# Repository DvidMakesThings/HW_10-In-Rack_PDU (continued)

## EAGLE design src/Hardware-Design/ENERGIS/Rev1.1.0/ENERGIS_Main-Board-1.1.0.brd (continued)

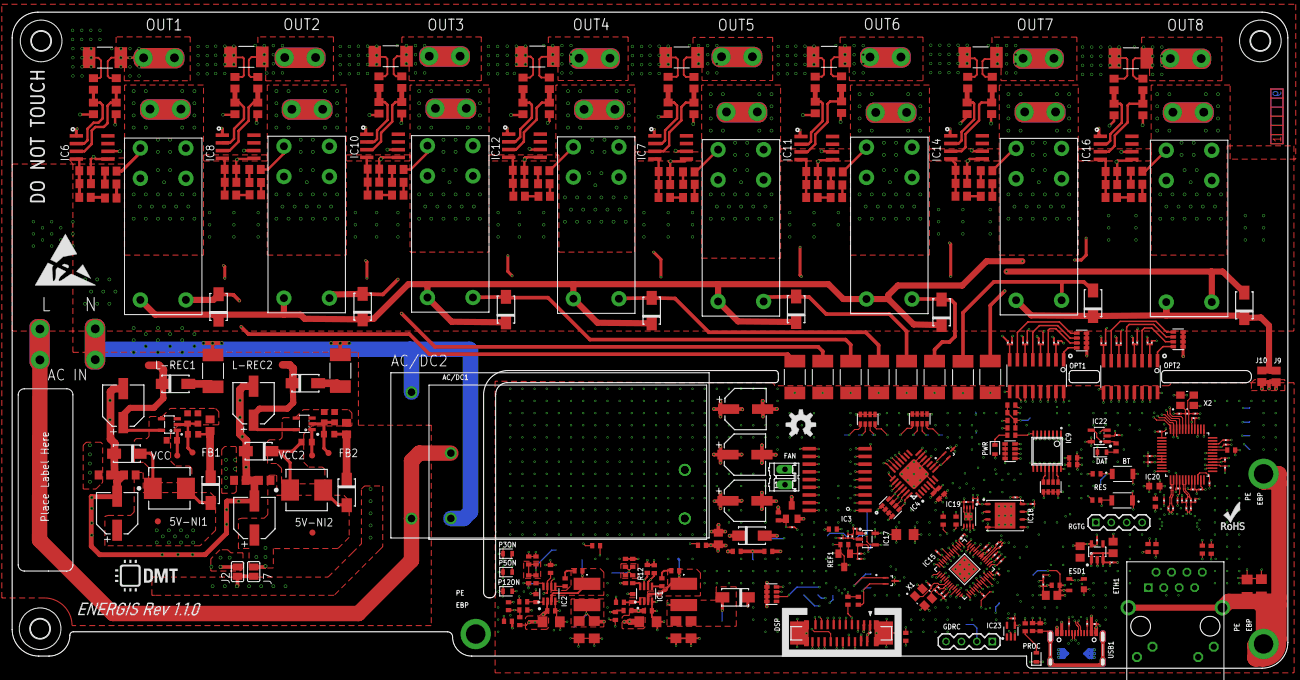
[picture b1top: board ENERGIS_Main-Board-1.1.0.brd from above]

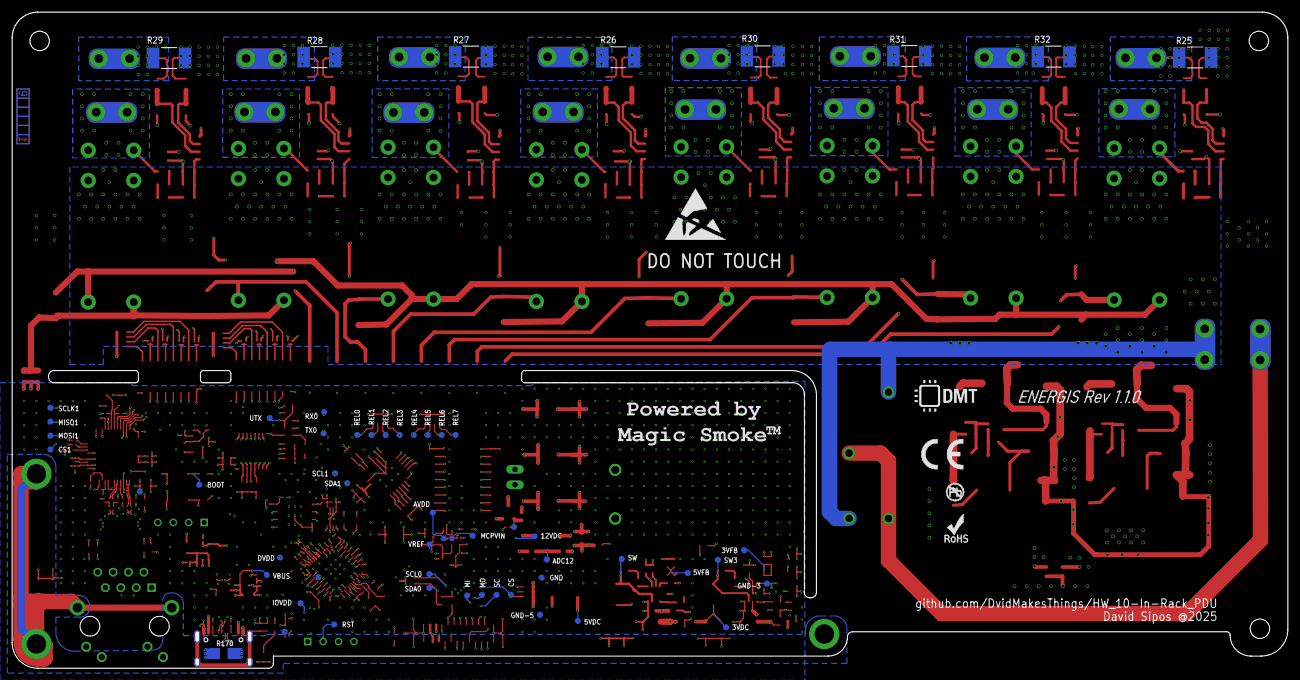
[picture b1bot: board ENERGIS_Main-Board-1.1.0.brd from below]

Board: 6 copper layers, 210.0 x 108.0 mm, 455 parts (62 on the bottom side), 254 nets.

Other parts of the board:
U$1, U$2: DNI; ESD_10.00
U$3, U$4, U$6: DNI; 3,2
U$5, U$7: DNI; DMT
U$10: DNI; OSHW-LOGO-M
U$11, U$14: DNI; ROHS_LOGO_0.18_IN
U$12: DNI; CE_5MM
U$13: DNI; NO_PB_LOGO_0.120
U$15: DNI; SMOKE

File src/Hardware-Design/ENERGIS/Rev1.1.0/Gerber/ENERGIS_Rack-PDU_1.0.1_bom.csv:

Comment,Designator,Footprint,LCSC Part #
0.002R 1%,R25 R26 R27 R28 R29 R30 R31 R32 R35 R43 R51 R67 R75 R83 R99 R115,2512,C728320
0R 1%,J8 J9 J10,0805,C17477
0R 1%,R17 R18 R19 R20 R21 R22 R23 R24,2512,C25469
0R 1%,R57 R91,0402,C17168
1K 1%,R16,0201,C270365
1K 1%,R33 R34 R40 R41 R42 R48 R49 R50 R56,0805,C17513
1K 1%,R59,0201,C270365
1K 1%,R63 R64,_0603X4-1206,C110021
1K 1%,R65 R66 R72 R73 R74 R80 R81 R82 R88 R97 R98 R104,0805,C17513
1K 1%,R112,0402,C11702
1K 1%,R113 R114 R120,0805,C17513
1K 1%,R122 R123 R151,0402,C11702
1K 1%,R153 R154 R155 R156 R157 R158 R159,0201,C270365
1K 1%,R163,0402,C11702
1M 1%,R110,1206,C17927
1M 1%,R131,0402,C26083
1M 1%,R144,0201,C295786
1N4007,D9 D10 D12 D13,SMA/DO-214AC,C727081
1mH,L3 L5,L-6.6X6.6,C168049
1nF 25V,C106 C107 C108 C109 C110 C111 C112 C113,0201,C7694325V
1nF 50V,C5 C51,0603,C1588
1uF 16V,C102,0201,C307385
1uF 25V,C60 C104,0402,C52923
1uF 50V,C45 C57,0805,C28323
2.2K 1%,R121,0201,C473508
2.2uF 50V,C21 C46,0603,C913904
2.2uF 400V,C35 C47,6.3X7.7(DXL),C3345109
2.4K 1%,R148,0402,C25882
3.3K 1%,R130 R149,_0603X4-1206,C1734380
3.3R 1%,R133 R134 R135 R136,0201,C158547
4.2uH,L2,SRR5228A,
4.7K 1%,R109 R129 R145,0201,C270346
4.7nF 50V,C78,0402,C1538
4.7uF 25V,C85,0402,C22367824
4.9uH,L1,SRR5228A,
4.99K 1%,R60 R61 R105 R107,0603,C23046
5.1K 1%,R124 R125,0201,C274341
6.8nF 50V,C81 C82,0201,C285015
7.5K 1%,R6 R12,0402,C25918
8.2K 1%,R150,0402,C25924
9.09K 1%,R4,0402,C11549
10K 1%,R2,0402,C25744
10K 1%,R89 R90 R93,_0603X4-1206,C110924
10K 1%,R95,0402,C25744
10K 1%,R96 R108,0805,C17414
10K 1%,R126 R127,0201,C473048
10K 1%,R132 R147 R162 R164,0402,C25744
10R 1%,R7 R9,0402,C25077
10R 1%,R152,0201,C270817
10uF 50V,C65 C97 C99,0805,C440198
12.4K 1%,R143,R0201,
12.7K 1%,R14,0402,C25853
15pF 50V,C58 C59,0201,C22374851
18pF 50V,C86 C87,0201,C62164
20K 1%,R8,0402,C25765
22nF 50V,C80,0402,C1532
22uF 25V,C1 C2 C14 C15 C17 C18,1206,C12891
25MHz,X2,WE-XTAL_CFPX-180,C9006
27R 1%,R15 R160,0201,C473051
33K,R10,0402,
33nF 50V,C24 C25 C26 C27 C28 C29 C30 C31 C32 C36 C37 C38 C39 C40 C41 C42 C43 C44 C48 C49 C50 C54 C55 C56,0805,C107150
33pF 50V,C11 C12,0402,C107005
39R 1% 2W,R62 R106,2512,C175263
40.2K 1%,R11 R13,0402,C25893
49.9R 1%,R137 R138 R139 R140,0201,C155744
100K 1%,R3 R5 R94,0402,C25741
100K 1%,RN1 RN2,_0603X4-1206,C110374
100nF 25V,C3 C4 C6 C7 C8 C9 C19 C20 C33 C34,0402,C56392
100nF 25V,C61 C62 C63 C64,0201,C76939
100nF 25V,C66,0402,C56392
100nF 25V,C67 C68 C69 C70 C71 C72 C73 C74 C75 C76 C77,0201,C76939
100nF 25V,C79,0402,C56392
100nF 25V,C84 C88 C89 C90 C91 C92 C93 C94 C95 C96 C98 C100 C101 C103,0201,C76939
100uF 25V,C10 C13 C16,6.3X7.7(DXL),C267469
100uF 50V,C23 C53,6.3X7.7(DXL),C3151829
220nF 50V,C22 C52,0805,C5378
470K 1%,R36 R37 R38 R39 R44 R45 R46 R47 R52 R53 R54 R55 R68 R69 R70 R71 R76 R77 R78 R79 R84 R85 R86 R87 R100 R101 R102 R103 R116 R117 R118 R119,0805,C17709
470R 1%,R141 R142 R146,0402,C25117
ABM8-272-T3 12MHz,X1,WE-XTAL_CFPX-180,C20625731
ACPL-247-500E ,OPT1 OPT2,SO16,C188681
AFC11-S20ICC-00 ,DSP,FPC20,C11073
B3U-1000P ,BOOT RESET,B3U-1000P,C231329
BLM18EG221TN1D,L4,0603,C113025
Blue,DAT,LED-0603,C965807
C1206C102KGRACTM,C83,C1206,
CAT24C256HU4IGT3,IC19,SON50P300X200X50-9T130X140N,C233771
DNI,R1 R58 R92,0402,
DNI,R111,R0201,
DNI,R161,0402,
G2RL-1A-E DC12 ,K1 K2 K3 K4 K5 K6 K7 K8,RELAY_G2RL-1A-E_DC5_OMR,C1564126
Green,P3ON P5ON P12ON PROC PWR,LED-0603,C965804
HLW8032,IC6 IC7 IC8 IC10 IC11 IC12 IC14 IC16,SO8,C128023
IRM-10-15 ,AC/DC2,IRM_15_12,C5439799
IRM_10_12,AC/DC1,IRM_10_12,C20618065
J1B1211CCD,ETH1,J1B1211CCD,C910371
JP,J2 J7,SJ,
LM4040B30FTA,REF1,SOT23,C460604
MBRA340T3G,D1 D2 D3 D4 D5 D6 D7 D8,SMA/DO-214AC,C26178
MCP6001RT-I/OT,IC17 IC22,SOT23-5,C154973
MCP23017T-E/ML ,IC4,QFN28[6X6]ML,C629439
MIC5504-3.3YM5 ,IC21,SOT23-5,C41348078
MOUNT-PAD-ROUND2.8,L_OUT1,2 8-PAD,
MOUNT-PAD-ROUND2.8,L_OUT2,2 8-PAD,
MOUNT-PAD-ROUND2.8,L_OUT3,2 8-PAD,
MOUNT-PAD-ROUND2.8,L_OUT4,2 8-PAD,
MOUNT-PAD-ROUND2.8,L_OUT5,2 8-PAD,
MOUNT-PAD-ROUND2.8,L_OUT6,2 8-PAD,
MOUNT-PAD-ROUND2.8,L_OUT7,2 8-PAD,
MOUNT-PAD-ROUND2.8,L_OUT8,2 8-PAD,
MOUNT-PAD-ROUND2.8,N_OUT1,2 8-PAD,
MOUNT-PAD-ROUND2.8,N_OUT2,2 8-PAD,
MOUNT-PAD-ROUND2.8,N_OUT3,2 8-PAD,
MOUNT-PAD-ROUND2.8,N_OUT4,2 8-PAD,
MOUNT-PAD-ROUND2.8,N_OUT5,2 8-PAD,
MOUNT-PAD-ROUND2.8,N_OUT6,2 8-PAD,
MOUNT-PAD-ROUND2.8,N_OUT7,2 8-PAD,
MOUNT-PAD-ROUND2.8,N_OUT8,2 8-PAD,
MOUNT-PAD-ROUND3.0,AC_L,3 0-PAD,
MOUNT-PAD-ROUND3.0,AC_N,3 0-PAD,
MP150GJ,IC5 IC13,SOT23-5,
MP2315GJ-Z ,IC1 IC2,SOT65P280X110-8N,C45889
NC,R128 R165,R0201,
RCLAMP0582BQTCT,D17 D18,SOT-523,C841193
RP2040,IC15,QFN56,C2040
SMAJ15A,D16,SMA/DO-214AC,C23424
SN74HC151PWR,IC9,TSSOP16,C2653837
SP0503BAHTG,ESD1,SOT143,C3040626
SS12,D15,SMA/DO-214AC,C727049
TP,3VDC 3VFB 5V-NI1 5V-NI2 5VDC 5VFB 12VDC AVDD CS0 CS1 DVDD FB-NI1 FB-NI2 GND GND-3 GND-5 IOVDD L-REC1 L-REC2 MISO0 MISO1 MOSI0 MOSI1 REL0 REL1 REL2 REL3 REL4 REL5 REL6 REL7 RX0 RX1 SCL0 SCL1 SCLK0 SCLK1 SDA0 SDA1 SW SW3 VBUS VNI1 VNI2 VREF,TP,
ULN2803AFWG,IC3,SO18,C845537
US1J-E3/61T ,D11 D14,SMA/DO-214AC,C44763
USB-TYPE-C-018 ,USB1,USB-C,C2927038
W25Q128JVPIQ,IC18,SON127P600X500X75-8N,C190862
W5500,IC20,LQFP48,C32843

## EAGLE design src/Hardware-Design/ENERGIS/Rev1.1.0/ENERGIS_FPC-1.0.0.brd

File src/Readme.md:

# ENERGIS - The Managed PDU Project for 10-Inch Rack - Design files

This repository contains source files for software and hardware designs related to the 10-Inch_Rack-PDU project.

## Contents

- **Software**: Source code for the software components.
- **Hardware**: Design files for the hardware components.

## Usage

1. Clone the repository.
2. Navigate to the `src` directory.
3. Follow the instructions in the respective subdirectories for software and hardware.

## License
This project is licensed under the GPL-3.0 License. See the [LICENSE](LICENSE) file for details.

## Contact
For questions or feedback:
- Email: [s.dvid@hotmail.com](mailto:s.dvid@hotmail.com)
- GitHub: [DvidMakesThings](https://github.com/DvidMakesThings)

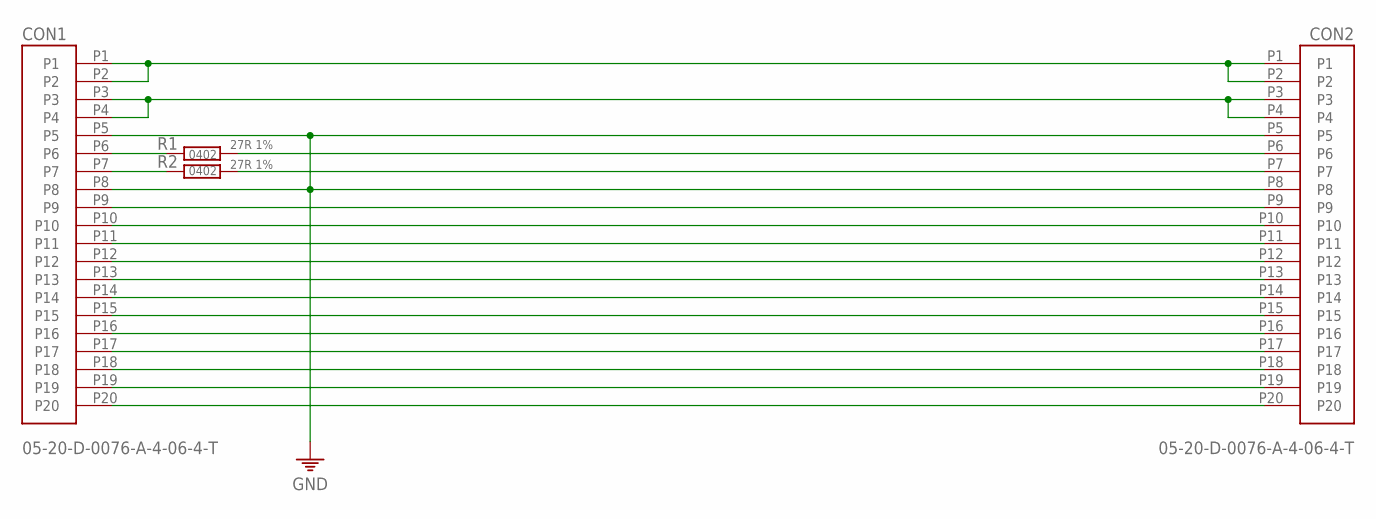
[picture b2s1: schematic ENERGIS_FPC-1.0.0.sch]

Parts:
CON1, CON2: 05-20-D-0076-A-4-06-4-T
R1, R2: 27R 1%; 0402

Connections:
GND: CON1.P5, CON1.P8, CON2.P5, CON2.P8
unnamed: CON1.P1, CON1.P2, CON2.P1, CON2.P2
unnamed: CON1.P3, CON1.P4, CON2.P3, CON2.P4
unnamed: CON1.P6, R1.1
unnamed: CON1.P7, R2.1
unnamed: CON1.P9, CON2.P9
unnamed: CON1.P10, CON2.P10
unnamed: CON1.P11, CON2.P11
unnamed: CON1.P12, CON2.P12
unnamed: CON1.P13, CON2.P13
unnamed: CON1.P14, CON2.P14
unnamed: CON1.P15, CON2.P15
unnamed: CON1.P16, CON2.P16
unnamed: CON1.P17, CON2.P17
unnamed: CON1.P18, CON2.P18
unnamed: CON1.P19, CON2.P19
unnamed: CON1.P20, CON2.P20
unnamed: CON2.P6, R1.2
unnamed: CON2.P7, R2.2

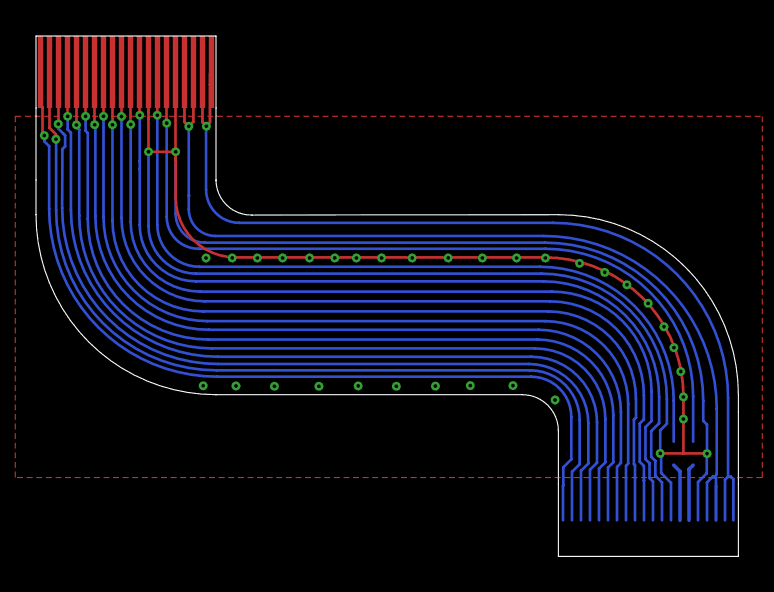
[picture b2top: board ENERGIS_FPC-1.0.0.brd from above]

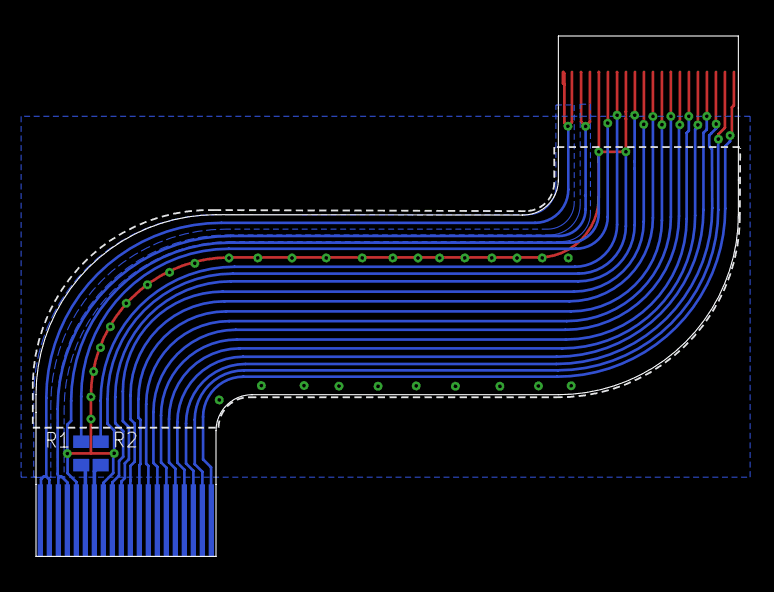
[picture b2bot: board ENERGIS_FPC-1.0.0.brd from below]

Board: 2 copper layers, 39.0 x 28.9 mm, 4 parts (3 on the bottom side), 19 nets.

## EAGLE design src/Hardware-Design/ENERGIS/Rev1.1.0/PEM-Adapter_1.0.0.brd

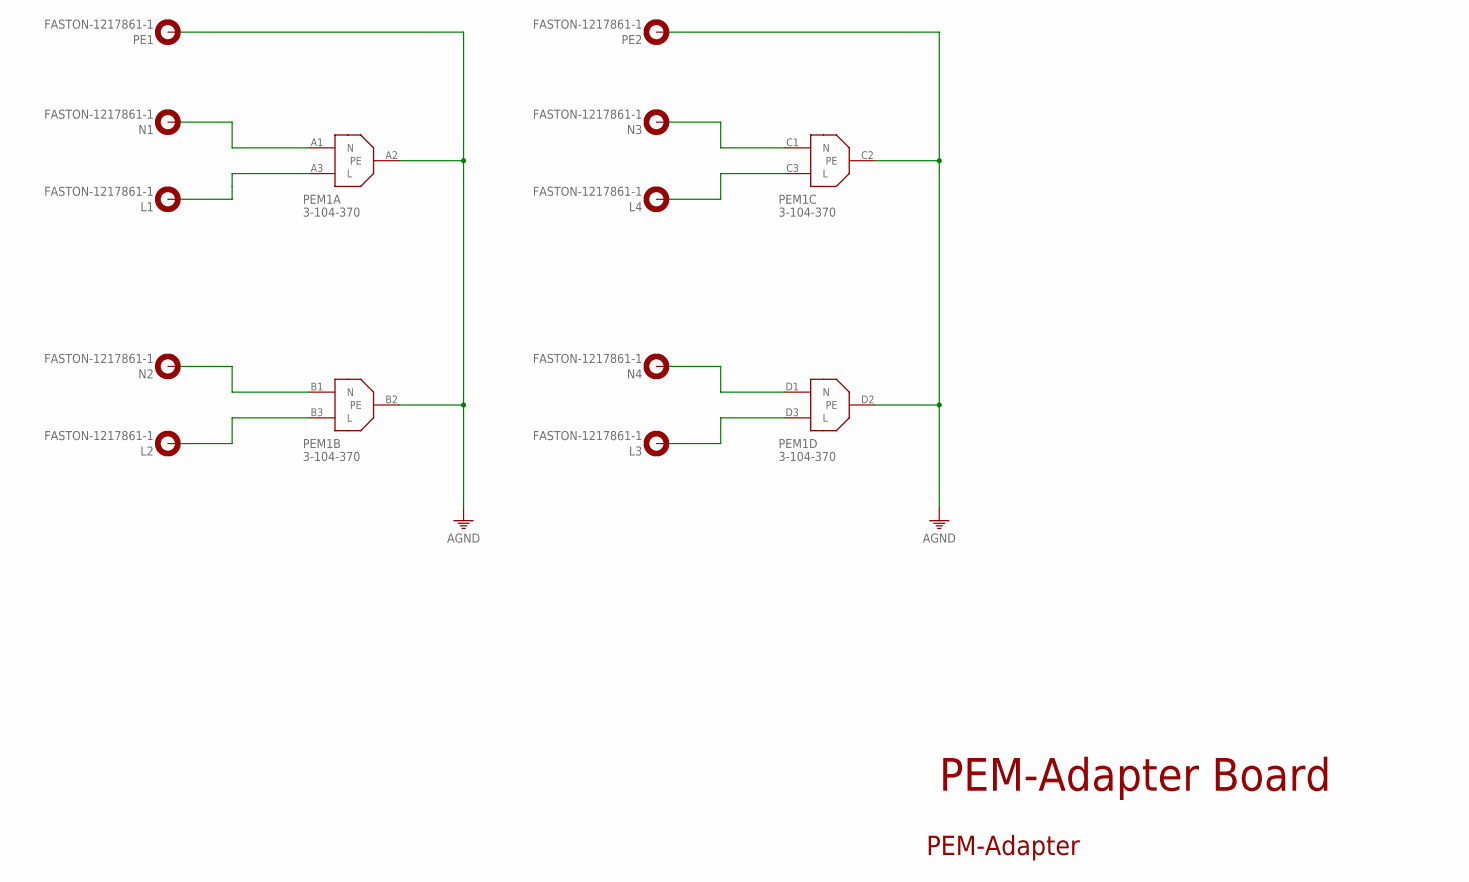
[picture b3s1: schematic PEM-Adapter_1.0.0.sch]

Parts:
L1, L2, L3, L4: FASTON-1217861-1; 1217861-1
N1, N2, N3, N4: FASTON-1217861-1; 1217861-1
PE1, PE2: FASTON-1217861-1; 1217861-1
PEM1: 3-104-370

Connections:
AGND: PE1.1, PE1.2, PE2.1, PE2.2, PEM1.A2 (PE), PEM1.B2 (PE), PEM1.C2 (PE), PEM1.D2 (PE)
L1: L1.1, L1.2, PEM1.A3 (L)
L2: L2.1, L2.2, PEM1.B3 (L)
L3: L4.1, L4.2, PEM1.C3 (L)
L4: L3.1, L3.2, PEM1.D3 (L)
N1: N1.1, N1.2, PEM1.A1 (N)
N2: N2.1, N2.2, PEM1.B1 (N)
N3: N3.1, N3.2, PEM1.C1 (N)
N4: N4.1, N4.2, PEM1.D1 (N)

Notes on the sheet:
PEM-Adapter Board
PEM-Adapter

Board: 2 copper layers, 15 parts (12 on the bottom side), 9 nets, no tracks yet.

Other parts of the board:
U$1, U$2: DNI; DMT
U$3, U$4: DNI; ROHS_LOGO_0.18_IN

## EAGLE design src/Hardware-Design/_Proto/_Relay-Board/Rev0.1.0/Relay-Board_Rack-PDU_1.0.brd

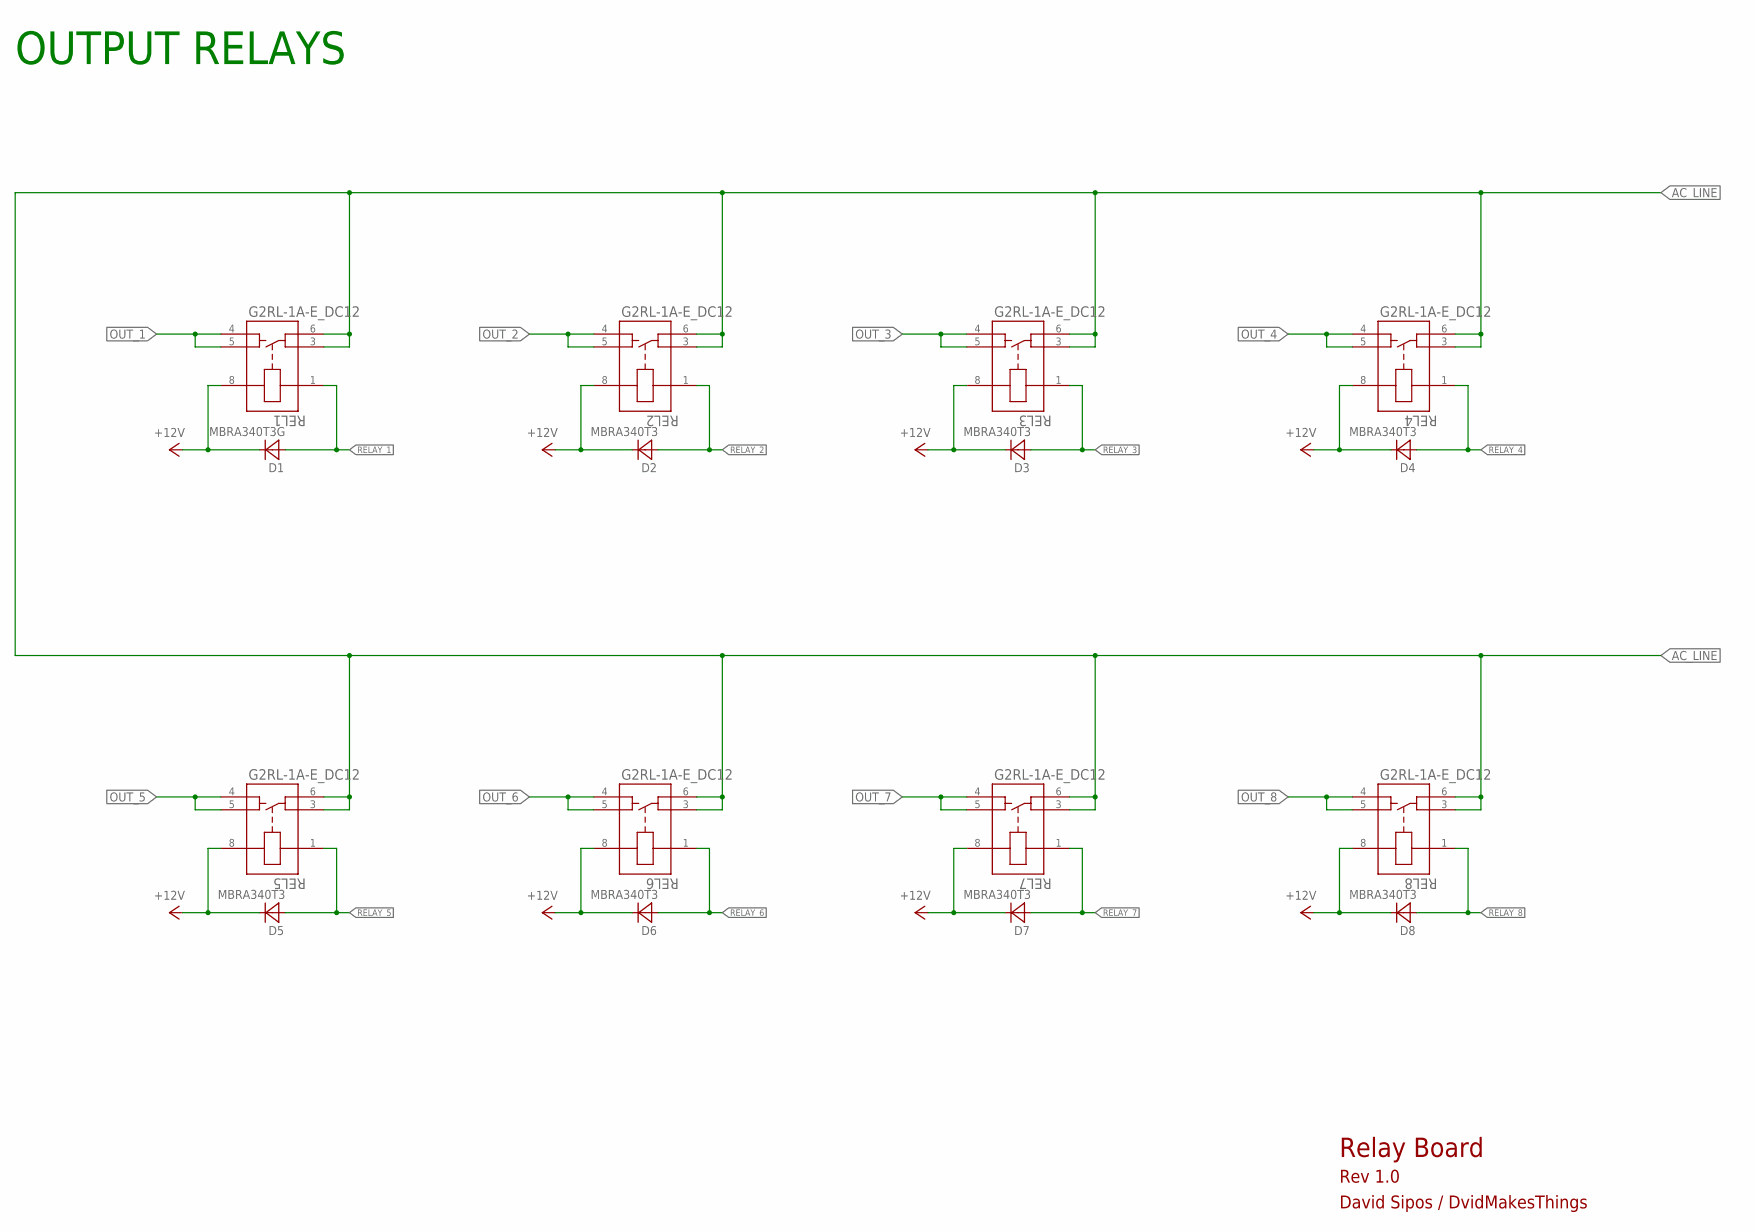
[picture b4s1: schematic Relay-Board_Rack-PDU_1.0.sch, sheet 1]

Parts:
D1: MBRA340T3G; SMA
D2, D3, D4, D5, D6, D7, D8: MBRA340T3; SMA
REL1, REL2, REL3, REL4, REL5, REL6, REL7, REL8: G2RL-1A-E_DC12; RELAY_G2RL-1A-E_DC5_OMR

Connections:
+12V: D1.C, D2.C, D3.C, D4.C, D5.C, D6.C, D7.C, D8.C, REL1.8, REL2.8, REL3.8, REL4.8, REL5.8, REL6.8, REL7.8, REL8.8; also elsewhere on the board
AC_LINE: REL1.3, REL1.6, REL2.3, REL2.6, REL3.3, REL3.6, REL4.3, REL4.6, REL5.3, REL5.6, REL6.3, REL6.6, REL7.3, REL7.6, REL8.3, REL8.6; also elsewhere on the board
OUT_1: REL1.4, REL1.5
OUT_2: REL2.4, REL2.5
OUT_3: REL3.4, REL3.5
OUT_4: REL4.4, REL4.5
OUT_5: REL5.4, REL5.5
OUT_6: REL6.4, REL6.5
OUT_7: REL7.4, REL7.5
OUT_8: REL8.4, REL8.5
RELAY_1: D1.A, REL1.1; also elsewhere on the board
RELAY_2: D2.A, REL2.1; also elsewhere on the board
RELAY_3: D3.A, REL3.1; also elsewhere on the board
RELAY_4: D4.A, REL4.1; also elsewhere on the board
RELAY_5: D5.A, REL5.1; also elsewhere on the board
RELAY_6: D6.A, REL6.1; also elsewhere on the board
RELAY_7: D7.A, REL7.1; also elsewhere on the board
RELAY_8: D8.A, REL8.1; also elsewhere on the board

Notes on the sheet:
OUTPUT RELAYS
Relay Board
Rev 1.0
David Sipos / DvidMakesThings

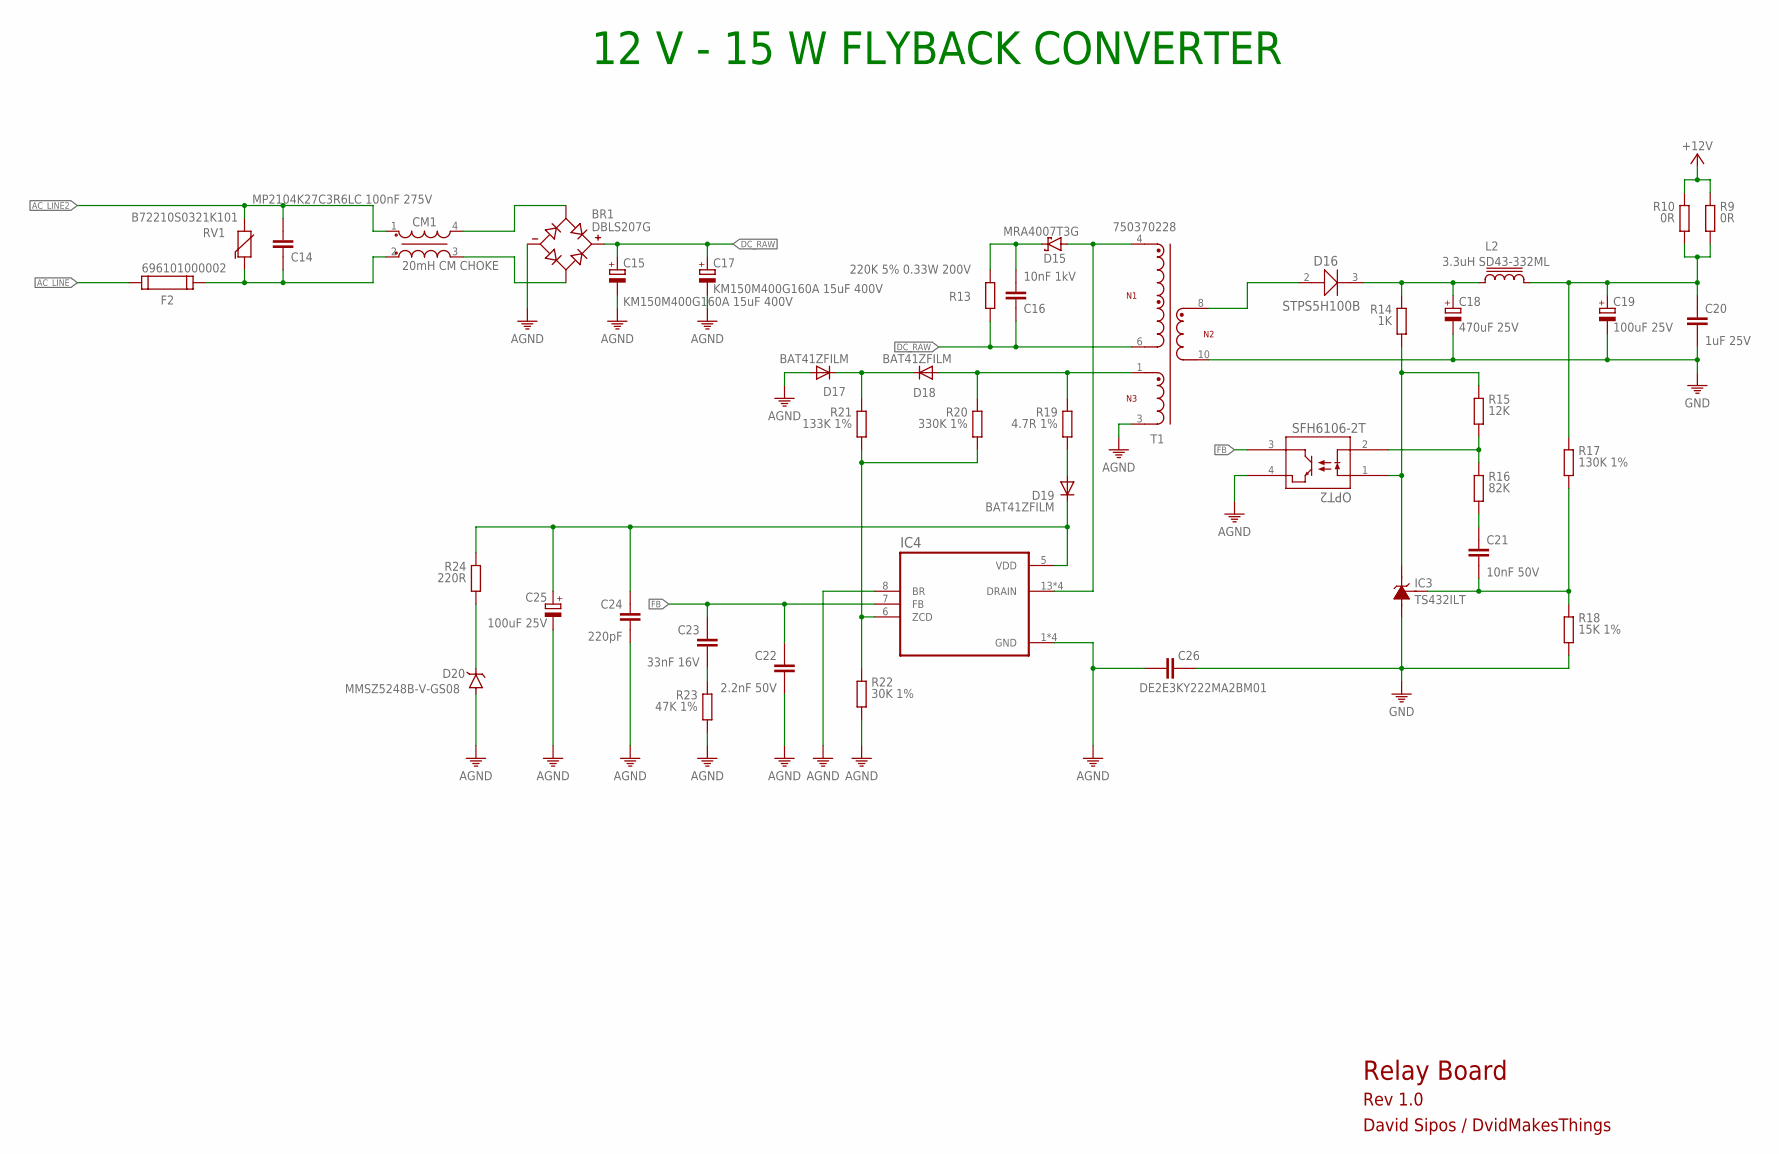
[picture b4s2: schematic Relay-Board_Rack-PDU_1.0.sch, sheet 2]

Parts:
BR1: DBLS207G; DIOB_DBLS207G
C14: MP2104K27C3R6LC 100nF 275V; 103-275V
C15, C17: KM150M400G160A 15uF 400V; CAPPRD550W110D1250H2500B
C16: 10nF 1kV; C1206
C18: 470uF 25V; CAPPRD508W65D1000H1100B
C19, C25: 100uF 25V; CAPPRD508W65D1000H1100B
C20: 1uF 25V; C0805
C21: 10nF 50V; C0805
C22: 2.2nF 50V; C0603
C23: 33nF 16V; C0603
C24: 220pF; C0805
C26: DE2E3KY222MA2BM01; AR21AC103K4R
CM1: 20mH CM CHOKE; WE-CMB_XS_744821120
D15: MRA4007T3G; SMA
D16: STPS5H100B; DPAK_STM
D17, D18, D19: BAT41ZFILM; SOD-123_MINI-SMA
D20: MMSZ5248B-V-GS08; DO214AC
F2: 696101000002
IC3: TS432ILT; SOT23
IC4: VIPER35HD
L2: 3.3uH SD43-332ML; INDUCTOR-BOURNS_SRN8040
OPT2: SFH6106-2T; SMD-4_SFH610X_VIS-M
R9, R10: 0R; 0805
R13: 220K 5% 0.33W 200V; 1206
R14: 1K; 0603
R15: 12K; 0603
R16: 82K; 0603
R17: 130K 1%; 0603
R18: 15K 1%; 0603
R19: 4.7R 1%; 0603
R20: 330K 1%; 0603
R21: 133K 1%; 0603
R22: 30K 1%; 0603
R23: 47K 1%; 0603
R24: 220R; 0805
RV1: B72210S0321K101; WE-VD_10MM_820412001
T1: 750370228; WE-OLSTM_EE20_L22.2W25H16

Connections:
+12V: R9.1, R10.1; also elsewhere on the board
AC_LINE: F2.1; also elsewhere on the board
AC_LINE2: C14.2, CM1.1, RV1.2
AGND: BR1.-, C15.2 (-), C17.2 (-), C22.2, C24.2, C25.2 (-), C26.1, D17.A, D20.A, IC4.1 (GND), IC4.2 (GND), IC4.3 (GND), IC4.4 (GND), IC4.8 (BR), OPT2.4, R22.2, R23.2, T1.3
DC_RAW: BR1.+, C15.1 (+), C16.1, C17.1 (+), R13.2, T1.6
FB: C22.1, C23.1, IC4.7 (FB), OPT2.3
GND: C18.2 (-), C19.2 (-), C20.2, C26.2, IC3.3, R18.2, T1.10; also elsewhere on the board
unnamed: C19.1 (+), C20.1, L2.2, R9.2, R10.2, R17.1
unnamed: BR1.AC1, CM1.4
unnamed: BR1.AC2, CM1.3
unnamed: C14.1, CM1.2, F2.2, RV1.1
unnamed: C16.2, D15.C, R13.1
unnamed: D15.A, IC4.13 (DRAIN), IC4.14 (DRAIN), IC4.15 (DRAIN), IC4.16 (DRAIN), T1.4
unnamed: D16.2, T1.8
unnamed: C18.1 (+), D16.3, L2.1, R14.1
unnamed: IC3.2, OPT2.1, R14.2, R15.1
unnamed: OPT2.2, R15.2, R16.1
unnamed: C21.1, R16.2
unnamed: C21.2, IC3.1, R17.2, R18.1
unnamed: C24.1, C25.1 (+), D19.C, IC4.5 (VDD), R24.1
unnamed: D19.A, R19.2
unnamed: D18.A, R19.1, R20.1, T1.1
unnamed: D17.C, D18.C, R21.1
unnamed: IC4.6 (ZCD), R20.2, R21.2, R22.1
unnamed: C23.2, R23.1
unnamed: D20.C, R24.2

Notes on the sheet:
12 V - 15 W FLYBACK CONVERTER
Relay Board
Rev 1.0
David Sipos / DvidMakesThings

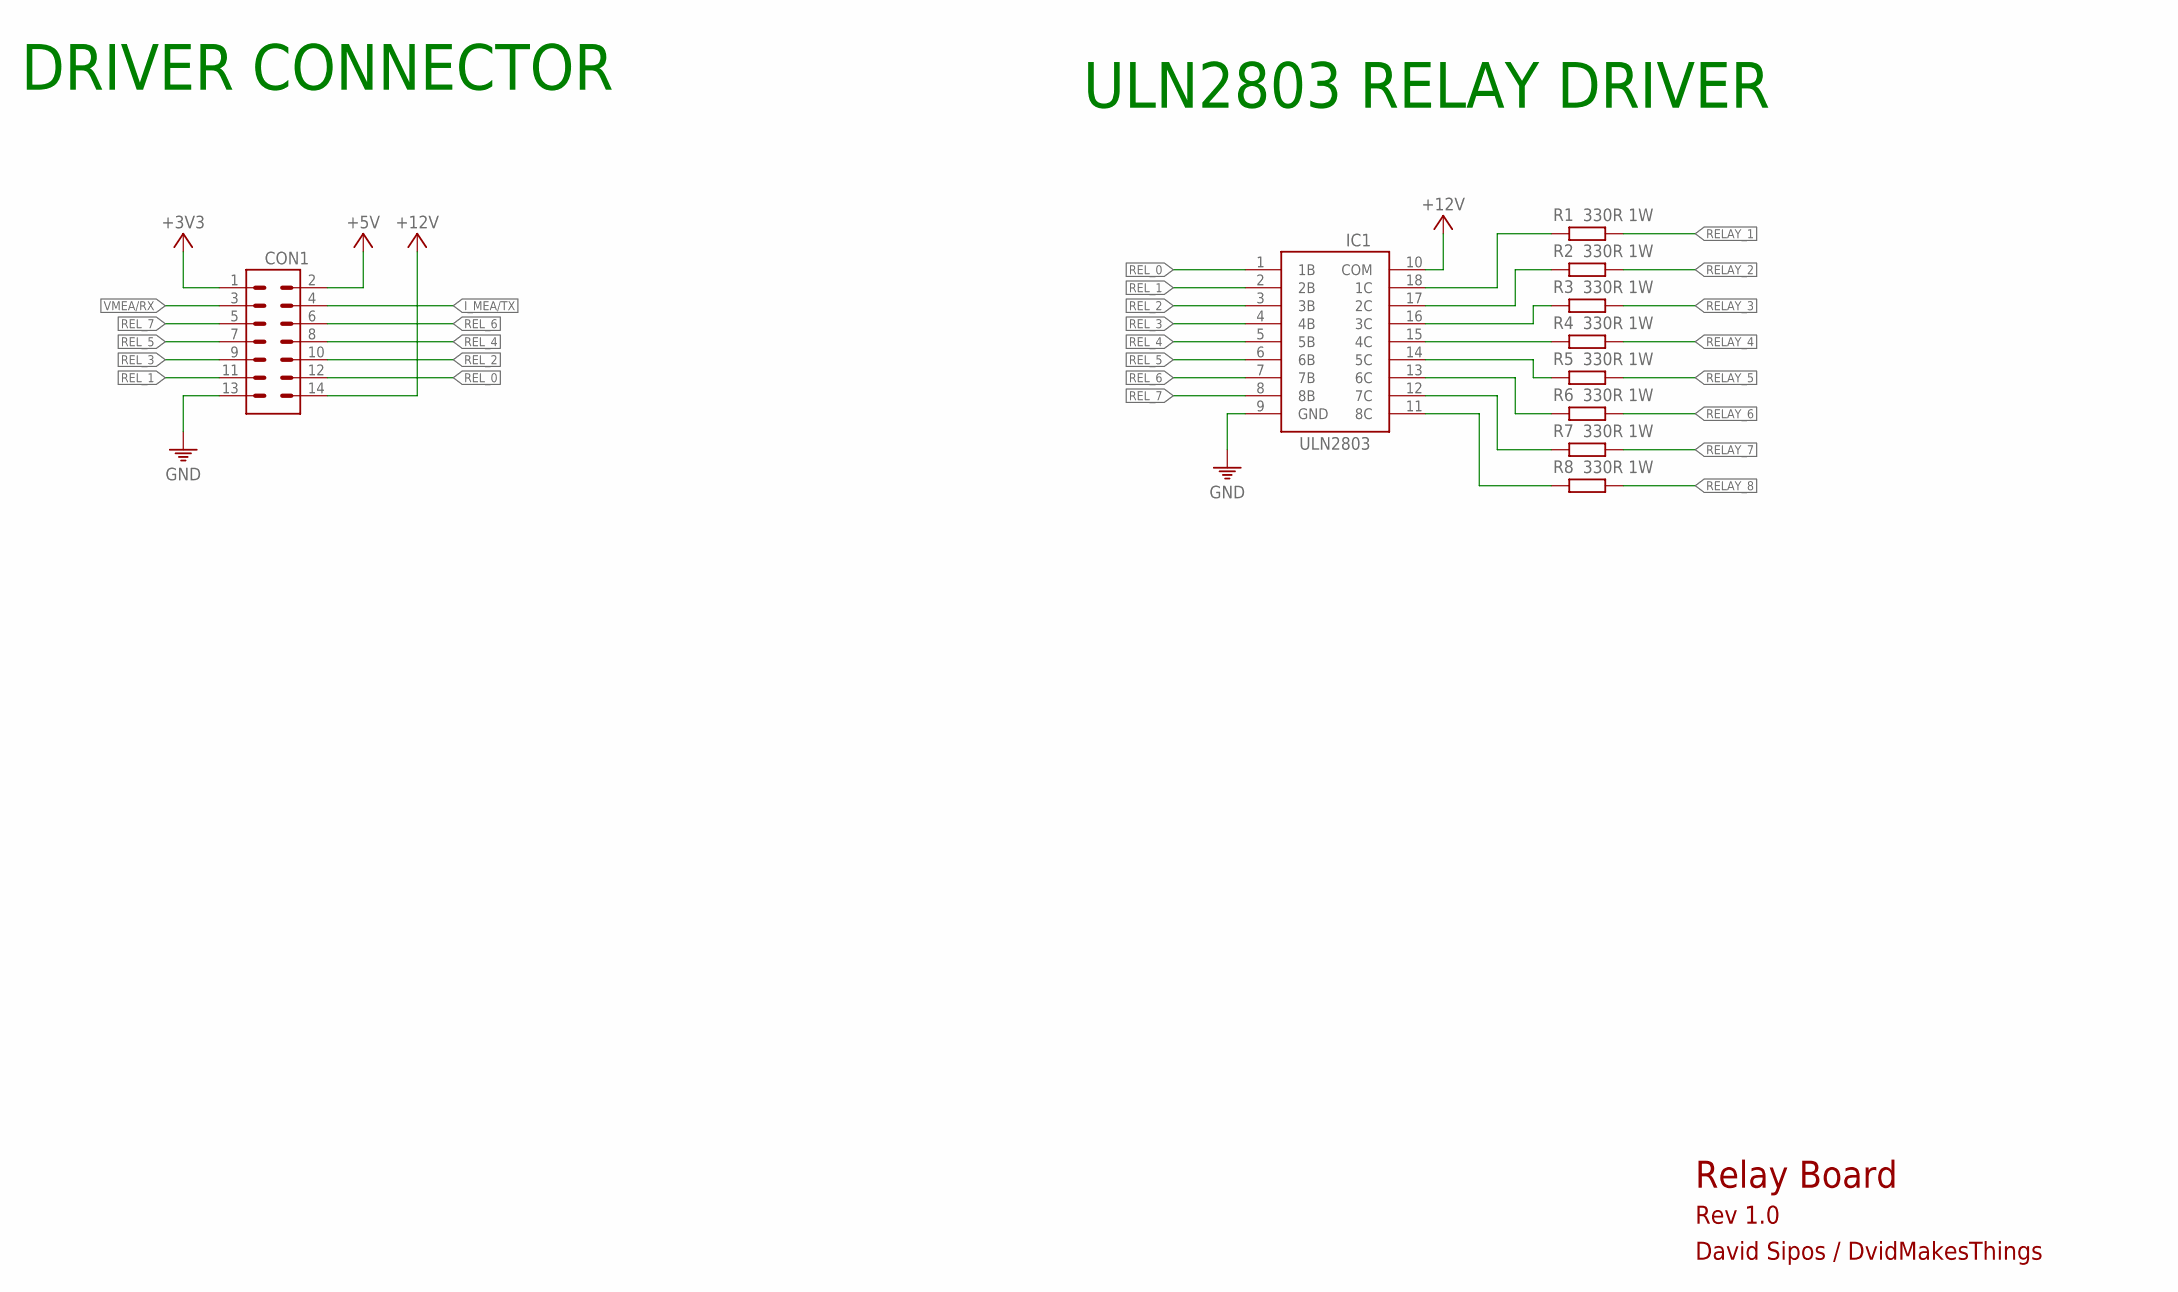
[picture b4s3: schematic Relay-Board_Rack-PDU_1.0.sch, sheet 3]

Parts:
CON1: CON-2X7; 2X7
IC1: ULN2803A; SO18
R1, R2, R3, R4, R5, R6, R7, R8: 330R 1W; 1206

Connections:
+3V3: CON1.1
+5V: CON1.2
+12V: CON1.14, IC1.10 (COM); also elsewhere on the board
GND: CON1.13, IC1.9 (GND); also elsewhere on the board
I_MEA/TX: CON1.4
unnamed: IC1.18 (1C), R1.1
unnamed: IC1.17 (2C), R2.1
unnamed: IC1.16 (3C), R3.1
unnamed: IC1.15 (4C), R4.1
unnamed: IC1.14 (5C), R5.1
unnamed: IC1.13 (6C), R6.1
unnamed: IC1.12 (7C), R7.1
unnamed: IC1.11 (8C), R8.1
RELAY_1: R1.2; also elsewhere on the board
RELAY_2: R2.2; also elsewhere on the board
RELAY_3: R3.2; also elsewhere on the board
RELAY_4: R4.2; also elsewhere on the board
RELAY_5: R5.2; also elsewhere on the board
RELAY_6: R6.2; also elsewhere on the board
RELAY_7: R7.2; also elsewhere on the board
RELAY_8: R8.2; also elsewhere on the board
REL_0: CON1.12, IC1.1 (1B)
REL_1: CON1.11, IC1.2 (2B)
REL_2: CON1.10, IC1.3 (3B)
REL_3: CON1.9, IC1.4 (4B)
REL_4: CON1.8, IC1.5 (5B)
REL_5: CON1.7, IC1.6 (6B)
REL_6: CON1.6, IC1.7 (7B)
REL_7: CON1.5, IC1.8 (8B)
VMEA/RX: CON1.3

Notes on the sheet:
Relay Board
Rev 1.0
David Sipos / DvidMakesThings
DRIVER CONNECTOR
ULN2803 RELAY DRIVER

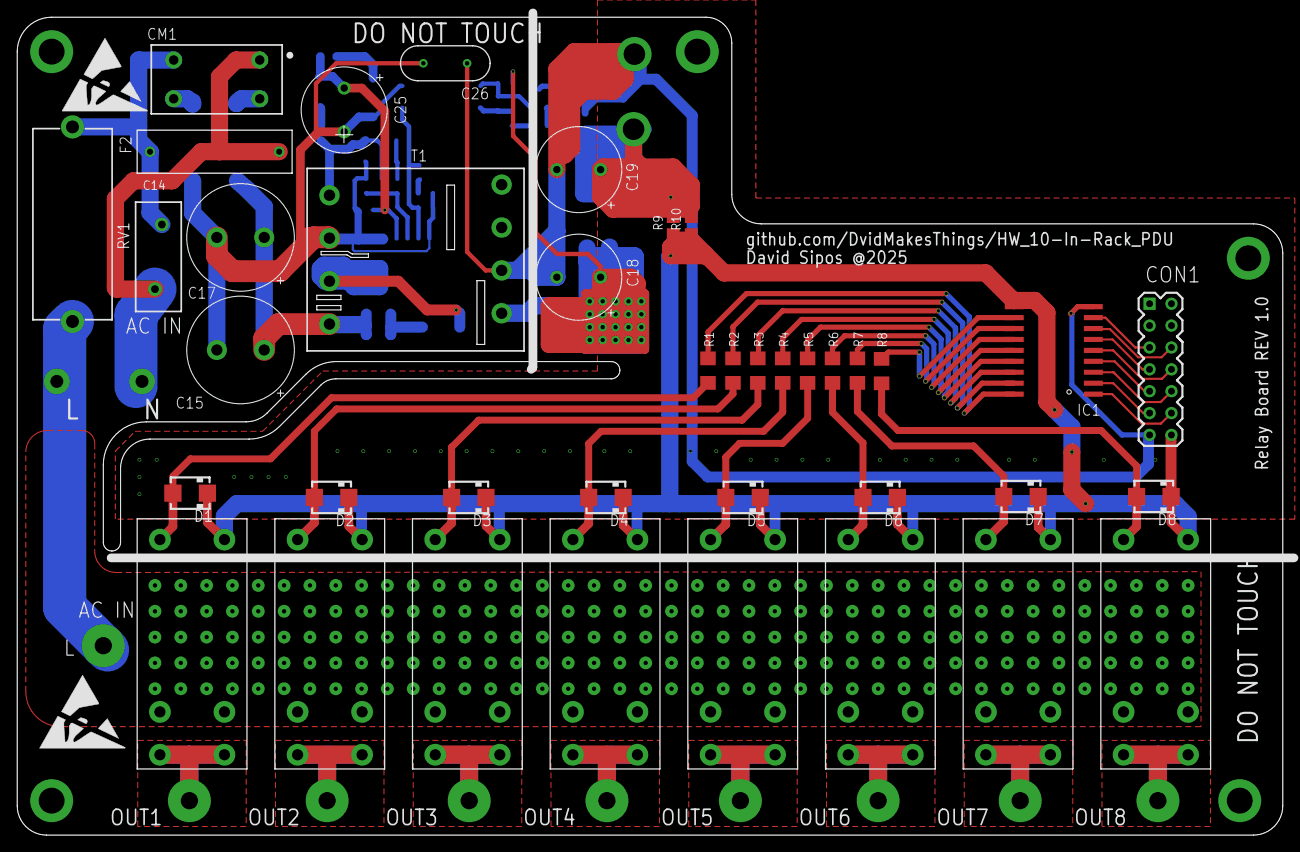
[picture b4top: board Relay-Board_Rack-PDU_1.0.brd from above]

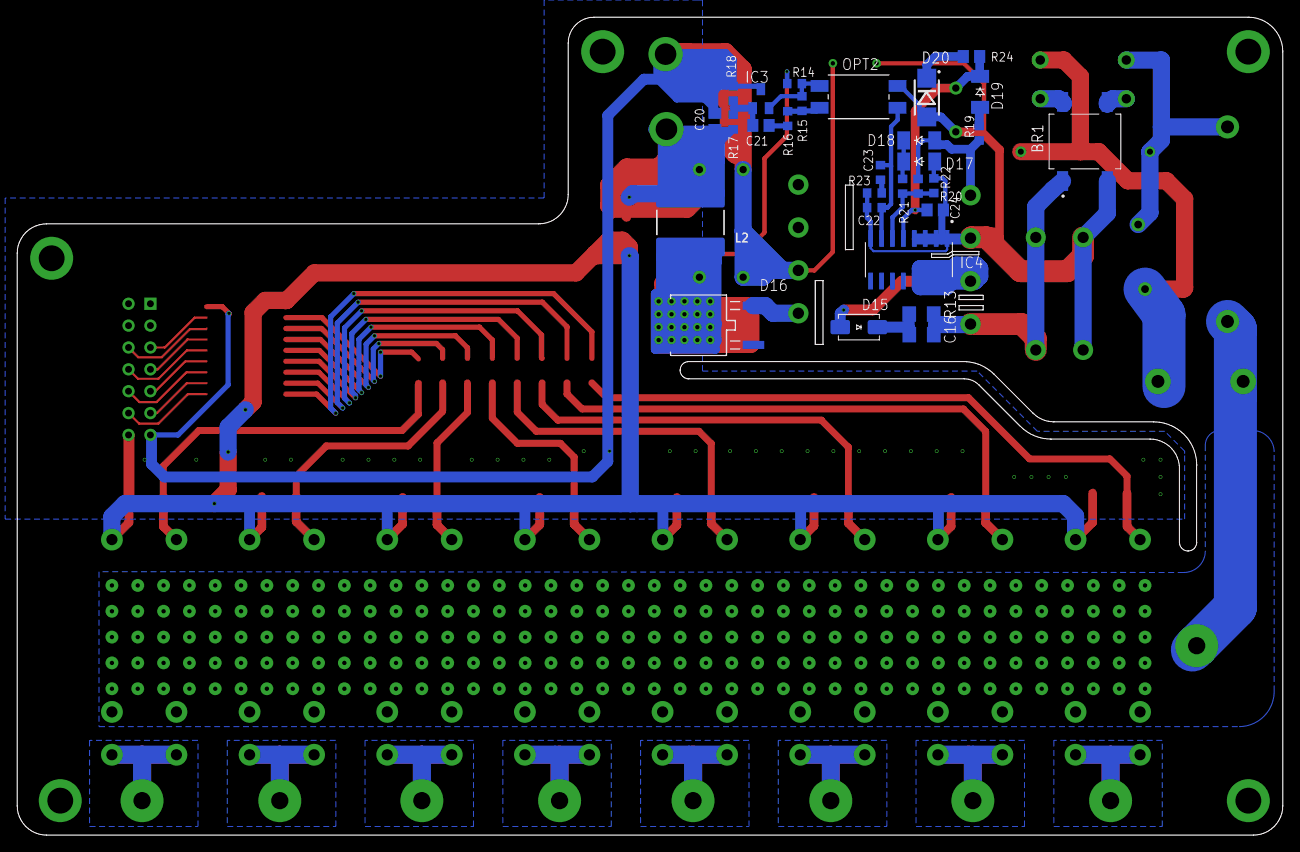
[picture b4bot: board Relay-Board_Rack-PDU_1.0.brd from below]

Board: 2 copper layers, 147.0 x 95.0 mm, 70 parts (29 on the bottom side), 58 nets.

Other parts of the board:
U$1, U$2: ESD_10.00
